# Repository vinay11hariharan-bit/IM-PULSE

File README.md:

# IM-PULSE — Cuffless Blood Pressure & Cardiac Monitor

**🏆 Top-10 finalist, EDL 2026, IIT Bombay**

IM-PULSE is a compact, portable biomedical monitor built in the Electronic Device Lab (EDL) course at IIT Bombay. It acquires ECG and two arterial pulse waveforms (APW, from bioimpedance/IPG) through six electrodes on the chest and foot. It detects ECG R-peaks and APW feet on board, measures **pulse transit time (PTT)** and **pulse wave velocity** (4–10 m/s), and estimates **blood pressure without a cuff** using an XGBoost model. Data streams wirelessly to a laptop, which shows a live PyQt6 dashboard and serves the vitals to any browser through a Flask web server.

The aim is a convenient alternative to bulky inflatable-cuff BP monitors and conventional ECG / Bio-Z instruments, for frequent cardiac monitoring where such equipment is unavailable or unaffordable.

## System Overview

```
 6 electrodes (chest, foot, abdomen ref.)
        │
 2 × MAX30001 AFE  ── ECG + BioZ @ 128 Hz ──┐
                                            ▼  SPI
 INA219 power monitor ── I2C ──►  STM32F411 Black Pill
                                   • Pan-Tompkins R-peak detection (ECG)
                                   • APW foot detection (proximal: ECG-triggered cubic fit,
                                     distal: morphological V-shape detector)
                                   • 36-byte packet every 8 ms
                                            │  UART 57600
                                            ▼
                                   ESP32  ── UDP broadcast, port 12345 (Wi-Fi)
                                            │
                                            ▼
                     Laptop: display.py (PyQt6)                webserver.py (Flask + ngrok)
                     • PTT, PWV, heart rate, HRV       ──►     • browser dashboard on LAN
                     • ECG morphology (QRS, PR, QTc)   JSON    or the internet
                     • XGBoost BP estimate
```

| | |
|---|---|
| Acquisition | 2 × MAX30001 (ECG + bioimpedance), 128 Hz per channel |
| Processing MCU | STM32F411CEU6 (Cortex-M4F, 100 MHz) |
| Wireless | ESP32, UART → UDP over Wi-Fi |
| Power | 2 × 18650 Li-ion with BMS, INA219 telemetry |
| Hardware | Custom two-layer PCB (KiCad), 3D-printed enclosure with acrylic panels |
| Host software | Python: PyQt6 + pyqtgraph GUI, Flask dashboard, XGBoost BP model |

## Repository Layout

| Path | Contents |
|---|---|
| [`src/stm32_blackpill/`](src/stm32_blackpill) | Acquisition and on-board DSP firmware (Arduino / STM32duino) |
| [`src/esp32_bridge/`](src/esp32_bridge) | UART-to-UDP Wi-Fi bridge firmware |
| [`src/host_app/`](src/host_app) | Desktop GUI (`display.py`), web dashboard (`webserver.py`), trained BP model |
| [`pcb/`](pcb) | KiCad project for the device PCB, footprints, layer prints, BMS build photos |
| [`3d_models/`](3d_models) | Enclosure STL and laser-cut acrylic panel DXFs |
| [`others/`](others) | [User manual](others/USER_MANUAL.md), build photos, MATLAB simulations, BMS docs, write-ups |
| [`reports/`](reports) | Milestone reports M0–M4 |
| [`bom.xls`](bom.xls) | Bill of materials |

Every folder has its own README with details. Each firmware/software folder also has a `SETUP.md` with flashing or run instructions.

## Quick Start

1. **STM32** — flash `src/stm32_blackpill/stm32_blackpill.ino` with the STM32duino core ([setup](src/stm32_blackpill/SETUP.md)).
2. **ESP32** — put your Wi-Fi SSID and password in `src/esp32_bridge/esp32_bridge.ino`, then flash it ([setup](src/esp32_bridge/SETUP.md)).
3. **Laptop** — join the same network, then run:
   ```sh
   cd src/host_app
   pip install -r requirements.txt
   python display.py      # live GUI + signal processing
   python webserver.py    # in a second terminal: browser dashboard on port 5000
   ```
   See [`src/host_app/SETUP.md`](src/host_app/SETUP.md) for virtual-environment and ngrok setup, and the [user manual](others/USER_MANUAL.md) for electrode placement.

## Build Photos

| PCB | Assembled device | Enclosure |
|---|---|---|
|  |  |  |

## Team

IM-PULSE (group MON-04): Yashvardhan Khandegar, Sudhindra Sahoo, Jahnvi Sharma, Vinay Hariharan, Krunal Vaghela.

---

# Reflections, Challenges & Future Work

### Project Status Summary

| Specification / Requirement | Status | Remarks / Justification |
|:----------------------------|:------:|:------------------------|
| 4-electrodes only, two on each wrist | ⚠️ Incomplete | Wrist APW unviable — instead we used 6 electrodes (chest (2) + foot (2) + abdomen reference (2)) |
| Compact portable table-top unit (bio-signal acquisition, processing & wireless) | ✅ Complete | |
| Onboard ECG R-peak & APW foot detection on STM32 | ✅ Complete | |
| Plot ECG + proximal & distal APW, verify reliability | 🔶 Partial | Chest ECG & APW reliable; foot APW less regular due to lower SNR — heart rate cross-verified with clinical device |
| Obtain Pulse Wave Velocity in typical range (4–10 m/s) | ✅ Complete | |
| Derive other health parameters from PTT and cross-verify them | 🔶 Partial | We focused on blood pressure as research has shown negative PTT–BP correlation; model trained on single subject (data limitation) |

---

### Challenges & How We Overcame Them

#### Dual-Purpose BioZ (Respiration + APW for PTT)

**Problem:** The MAX30001's BioZ channel conflates respiration and blood-related IPG signals. Respiration-focused acquisition introduced a DC offset and saturation, distorting the APW signal needed for PTT computation.

**Solution:** We reconfigured the channel for blood IPG (APW) by removing respiration-centric filtering, applying a band-pass filter (~0.8–5 Hz), and syncing the APW with ECG R-peaks to correctly compute PTT.

---

#### Electrode Placement & Signal Integrity

**Problem:** Accurate proximal–distal APW measurement required very precise electrode placement, and signals were frequently distorted by environmental interference from nearby charged sources.

**Solution:** After extensive experimentation, we finalized electrode positions over the chest (proximal) and left foot (distal) arteries to capture stable APW. Interference was eliminated by grounding nearby charged objects in the measurement environment.

---

#### PTT–BP Modeling with a Custom Dataset

**Problem:** No reliable publicly available dataset exists for heart-to-foot PTT vs blood pressure correlation. Our raw measurements were noisy and unstructured, making it difficult to train a meaningful model.

**Solution:** We collected approximately 200 samples using reference blood pressure measurements alongside our PTT readings, cleaned and processed the raw data, and trained a regression model to learn the PTT–BP mapping and extract meaningful patterns.

---

#### STM32 Chip Mismatch (F411CE vs F401CE)

**Problem:** The BlackPill boards purchased were labelled STM32F411CE, but many units in the market are actually equipped with an STM32F401CE chip. This silent mismatch caused repeated code upload failures and cost significant debugging time before the root cause was identified.

**What We Learned:** Always verify the actual chip ID using STM32CubeProgrammer before beginning development. Physical markings on a board cannot always be trusted, especially with generic suppliers.

---

### Key Takeaways

**Technical:**
- Bio-signal acquisition requires careful analog front-end tuning — default configurations are rarely sufficient for multi-purpose sensors like the MAX30001.
- Electrode placement has a profound impact on signal quality; this is as much a physiological problem as an electronics one.
- Building a custom dataset from scratch is time-consuming but necessary when the target measurement (heart-to-foot PTT) does not have existing benchmarks.
- Hardware debugging (chip mismatches, board variants) can consume a disproportionate amount of time — always validate components early.

**Team & Process:**
- A modular PCB and software architecture paid off: when individual components failed or needed replacement, the rest of the system remained unaffected.
- Separating the signal processing pipeline from the hardware layer early allowed the software team to develop and test algorithms in parallel with PCB bring-up.
- Time lost on hardware issues compressed the software iteration cycles — future projects should budget extra time for hardware validation in the first two weeks.

---

## Incomplete Features & Future Work

### Features Not Completed Within the Course Timeline

- **Wrist-based APW measurement:** The original specification required only 4 electrodes placed on the wrists. Wrist APW turned out to be physiologically unviable for our sensing configuration — the signal was too weak and inconsistent for reliable PTT computation. This remains unresolved.
- **Multi-subject PTT–BP model:** The trained blood pressure model was built on data from a single subject due to time constraints. A generalised model requires a larger and more diverse dataset, which was not feasible within the semester.
- **Full cross-verification of derived health parameters:** While blood pressure estimation via PTT was partially achieved, other health parameters derivable from PTT (e.g., arterial stiffness index) were not implemented or verified.

---

### Concrete Future Work

**1. Expand the PTT–BP dataset and improve the model**
The current model is trained on a single subject (~200 samples), which limits its generalisability. Future work would involve collecting data across multiple subjects with varying age, fitness levels, and blood pressure ranges, and retraining the model. A more robust architecture (e.g., a subject-adaptive or personalised calibration model) could significantly improve accuracy.

**2. Improve foot APW signal quality with better analog filtering**
The foot APW signal had lower SNR compared to the chest signal. This could be addressed by adding a programmable gain stage or a narrower band-pass filter specifically tuned for the distal IPG signal, implemented either in hardware (op-amp filter stage on PCB) or through tighter DSP filtering on the STM32.

**3. Investigate wrist-based electrode configuration**
The wrist APW failure could be revisited by exploring different electrode configurations (e.g., radial artery targeting) or switching to PPG-based sensing at the wrist as a complementary approach for PTT. This would bring the device closer to the original wearable specification.

**4. Reduce wireless latency for real-time monitoring**
The current UDP-over-WiFi transmission introduces latency that makes real-time waveform monitoring less smooth. Switching to a lower-latency protocol (e.g., BLE with a custom GATT profile) or implementing a lightweight compression scheme before transmission could improve the live display experience without requiring a wired connection.

**5. Onboard blood pressure display**
Currently, BP estimation requires post-processing on a connected laptop. Integrating a small OLED display on the device and running the trained model directly on the ESP32 (after model quantisation) would make the device fully self-contained and usable without a computer.

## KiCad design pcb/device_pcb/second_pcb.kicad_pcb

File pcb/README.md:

# PCB Design 

## Overview

The primary purpose of this PCB is to provide an organized and compact physical realization of the circuit. It is basically a Bio-Signal Acquisition Board. Most components are breakout/evaluation boards that are directly fixed onto the PCB using female header pins, with the PCB establishing the required electrical connections between them.

<!-- Board photo -->

<!-- Board photo -->

---

## Features & Design Choices

### Two-Layer PCB with Ground Planes
SMD components are placed on the top layer, with a ground plane on both the top and bottom layers. Using ground planes on both sides helps shield signals from noise and provides a stable return path. Placing all components on the top layer simplifies the assembly process for both SMD and Through-Hole components. The continuous ground plane on the bottom layer also aids in heat dissipation due to the larger copper area.

### Modular PCB Design
Since the main goal of this project is building the software stack for bio-signal processing, the PCB is designed to act as an integration unit for power and signal connections between different modules. This modular setup keeps the focus on algorithms and makes it easy to replace individual parts if they are damaged.

### Indicator LEDs & Breakout Pins for Debugging
Built-in test points in the form of indicator LEDs and breakout pins make it easier to monitor power and signal lines, and to troubleshoot issues using an oscilloscope or multimeter. 
- One red-colored POWER LED
- Two yellow-colored LEDs to indicate which of the MAX30001 has been selected
- There are a few pins broken-out from the STM32 and the ESP32 such as general GPIO, SPI/UART lines for expanding functionality as well as debugging.  

### Power Stability
The PCB requires a stable & regulated 5V input at its main screw terminal. The STM32 has onboard 5V to 3V3 regulator, which then distributes a stable 3V3 voltage to other components. Decoupling capacitors are placed at the power inputs and outputs of each module to filter out electrical noise and maintain stable voltage levels.

---

## Components & Signal Flow

### Bio-Signal Acquisition — MAX30001 (×2)
Two **Protocentral MAX30001** breakout boards are used for collecting:
- **ECG** (Electrocardiogram) signals
- **Bio-Z** (Bioimpedance) signals

Both boards interface with the STM32 via **SPI**.

### Main MCU — STM32 BlackPill
The STM32 serves as the central processing unit of the system. It:
- Receives raw bio-signal data from both MAX30001 boards over SPI
- Runs on-board DSP algorithms for **ECG R-peak detection** and **APW (Arterial Pulse Wave) foot detection**
- Communicates with the INA219 over **I2C**
- Transmits processed data to the ESP32 over **UART (TX/RX)**

### Power Monitoring — INA219
The **INA219** current/power sensor is connected to the STM32 via **I2C**. It provides real-time data on:
- Battery voltage
- Current draw

### Wireless Communication — ESP32
The **ESP32** is connected to the STM32 via **UART**. It:
- Receives data packets containing waveform data, detected special points (R-peaks, APW feet), and INA219 readings
- Generates a **Wi-Fi access point** for wireless connectivity
- Transmits data to connected clients (e.g., laptops) using the **UDP** protocol

---

## System Architecture

```
┌─────────────────┐     SPI      ┌────────────────────┐
│  MAX30001 #1    │─────────────▶│                    │
│  (ECG / Bio-Z)  │              │   STM32 BlackPill  │──── I2C ────▶ INA219
└─────────────────┘              │   (DSP + Control)  │
                                 │                    │──── UART ───▶ ESP32 ──▶ WiFi (UDP)
┌─────────────────┐     SPI      │                    │
│  MAX30001 #2    │─────────────▶│                    │
│  (ECG / Bio-Z)  │              └────────────────────┘
└─────────────────┘
```

---

## Communication Interfaces Summary

| Interface | Between | Purpose |
|-----------|---------|---------|
| SPI | STM32 ↔ MAX30001 (×2) | Bio-signal data acquisition |
| I2C | STM32 ↔ INA219 | Battery voltage & current monitoring |
| UART | STM32 ↔ ESP32 | Processed data transfer |
| UDP (Wi-Fi) | ESP32 ↔ Client Device | Wireless data streaming |

## Pin Connections
 
### MAX30001 Board 1 → STM32 (SPI)
 
| MAX30001 Pin | STM32 Pin | Notes |
|:-------------|:----------|:------|
| GND | GND | |
| VCC | 3V3 | |
| GND | GND | |
| INT2 | — | Not Connected |
| INT1 | PB10 | Interrupt line |
| FCLK | — | Not Connected (external CLK not used) |
| CS0 | PB0 | Chip Select |
| SCK | PA5 | SPI1 Clock |
| MOSI | PA7 | SPI1 MOSI |
| MISO | PA6 | SPI1 MISO |
 
### MAX30001 Board 2 → STM32 (SPI)
 
| MAX30001 Pin | STM32 Pin | Notes |
|:-------------|:----------|:------|
| GND | GND | |
| VCC | 3V3 | |
| GND | GND | |
| INT2 | — | Not Connected |
| INT1 | PA1 | Interrupt line |
| FCLK | — | Not Connected (external CLK not used) |
| CS0 | PA0 | Chip Select |
| SCK | PA5 | SPI1 Clock (shared) |
| MOSI | PA7 | SPI1 MOSI (shared) |
| MISO | PA6 | SPI1 MISO (shared) |
 
> **Note:** Both MAX30001 boards share the same SPI bus (SCK, MOSI, MISO). They are differentiated by their individual Chip Select (CS0) pins — PB0 and PA0 respectively.
 
### INA219 → STM32 (I2C)
 
| INA219 Pin | STM32 / Connection | Notes |
|:-----------|:-------------------|:------|
| VCC | 3V3 | |
| GND | GND | |
| SCL | PB6 | I2C1 Clock |
| SDA | PB7 | I2C1 Data |
| Vin+ | Battery (+) terminal | High-side current sensing |
| Vin− | Switch output | Connected via the power switch |
 
### ESP32 → STM32 (UART)
 
| ESP32 Pin | STM32 Pin | Notes |
|:----------|:----------|:------|
| TX2 | PA10 (RX1) | ESP32 transmits → STM32 receives |
| RX2 | PA9 (TX1) | STM32 transmits → ESP32 receives |
 
---
 
## Known Issues & Gotchas
 
### ⚠️ STM32F411CE vs STM32F401CE Chip Mismatch
 
The STM32 BlackPill boards purchased were labelled as **STM32F411CE**, however many units sold in the market are actually equipped with an **STM32F401CE** chip. This mismatch is not visible externally and caused significant time loss during development when code uploads were failing unexpectedly.
 
**Root cause:** Counterfeit or mislabelled boards — the chip inscription on the package does not always match the actual silicon inside.
 
**How to detect:** Open **STM32CubeProgrammer**, connect via ST-Link, and check the **Device ID** reported by the programmer. This will reveal the actual chip variant regardless of what is printed on the board.
 
**Fix:** Once the correct chip is identified (e.g., `STM32F401CE`), select the matching target in STM32CubeIDE / STM32CubeMX and re-generate the project configuration.
 
---
 
## Component Links
 
| Component | Supplier | Link |
|:----------|:---------|:-----|
| Protocentral MAX30001 ECG & Bio-Z Breakout (×2) | Protocentral | [protocentral.com](https://protocentral.com/product/protocentral-max30001/) |
| STM32F411CEU6 BlackPill (WeAct Studio) | Robu.in | [robu.in](https://robu.in/product/weact-studio-blackpill-stm32f411ceu6-f411-25m-hse-core-learning-board-micropython-development/) |
| STM32F411CEU6 Minimum System Board | Robu.in | [robu.in](https://robu.in/product/stm32f411ceu6-minimum-system-board-microcomputer-stm32-arm-core-board/) |
| INA219 Current/Power Monitor (CJMCU-219) | Robu.in | [robu.in](https://robu.in/product/cjmcu-219-ina219-i2c-interface-no-drift-bi-directional-current-power-monitoring-sensor-module/) |
| ESP32 WROOM-32 Development Board | Robu.in | [robu.in](https://robu.in/product/esp32-38pin-development-board-wifibluetooth-ultra-low-power-consumption-dual-core/) |
| ST-Link V2 Programmer (for flashing STM32) | Robu.in | [robu.in](https://robu.in/product/st-link-v2-programmer-for-stm8-and-stm32/) |
 
> **Note:** The MAX30001 is a Protocentral product and is not available on Robu.in. Purchase directly from [protocentral.com](https://protocentral.com/product/protocentral-max30001/).

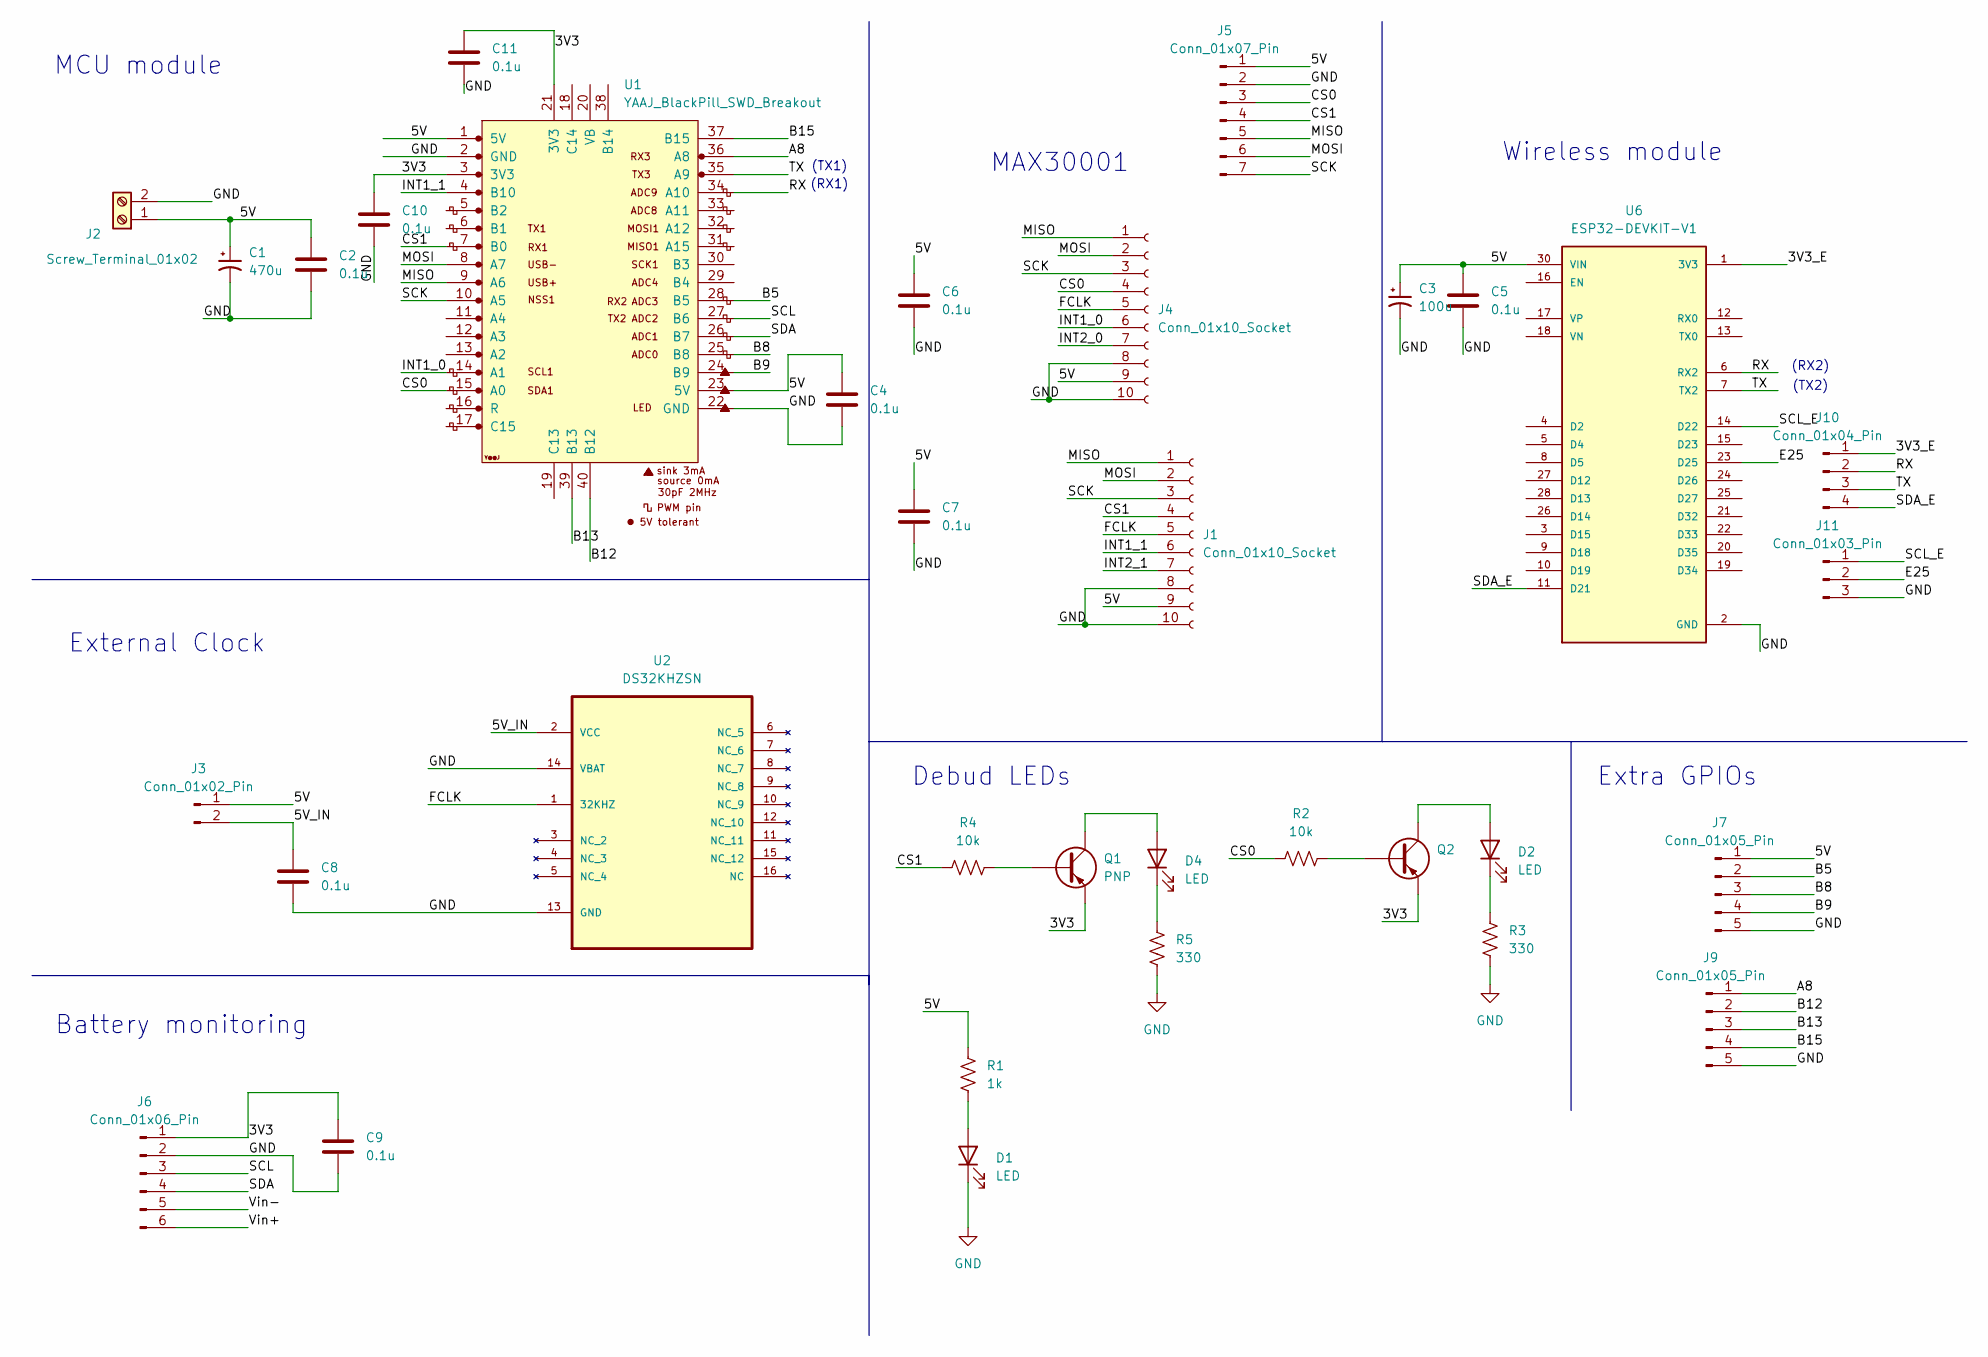
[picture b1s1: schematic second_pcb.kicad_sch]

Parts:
C1: 470u; CP_Radial_D8.0mm_P3.50mm
C2, C4, C5, C6, C7, C8, C9, C10, C11: 0.1u; C_0805_2012Metric
C3: 100u; CP_Radial_D5.0mm_P2.50mm
D1, D2, D4: LED; LED_1206_3216Metric
J1, J4: Conn_01x10_Socket; PinHeader_1x10_P2.54mm_Vertical
J2: Screw_Terminal_01x02; TerminalBlock_Phoenix_MKDS-3-2-5.08_1x02_P5.08mm_Horizontal
J3: Conn_01x02_Pin; PinHeader_1x02_P2.54mm_Vertical
J5: Conn_01x07_Pin; PinHeader_1x07_P2.54mm_Vertical
J6: Conn_01x06_Pin; PinHeader_1x06_P2.54mm_Vertical
J7, J9: Conn_01x05_Pin; PinHeader_1x05_P2.54mm_Vertical
J10: Conn_01x04_Pin; PinHeader_1x04_P2.54mm_Vertical
J11: Conn_01x03_Pin; PinHeader_1x03_P2.54mm_Vertical
Q1, Q2: PNP; TO-92L_HandSolder_modified
R1: 1k; R_0805_2012Metric
R2, R4: 10k; R_0805_2012Metric
R3, R5: 330; R_0805_2012Metric
U1: YAAJ_BlackPill_SWD_Breakout; YAAJ_BluePill_SWD_1
U2: DS32KHZSN; SOIC127P1034X267-16N; MPN DS32KHZSN#
U6: ESP32-DEVKIT-V1; MODULE_ESP32_DEVKIT_V1_modified; PARTREV N/A

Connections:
/3V3: C9.2, C10.2, C11.2, J6.1, Q1.1 (E), Q2.1 (E), U1.3 (3V3), U1.21 (3V3)
/3V3_E: J10.1, U6.1 (3V3)
/5V: C1.1, C2.2, C3.1, C4.2, C5.2, C6.2, C7.2, J1.9, J2.1, J3.1, J4.9, J5.1, J7.1, R1.1, U1.1 (5V), U1.23 (5V), U6.30 (VIN)
/5V_IN: C8.2, J3.2, U2.2 (VCC)
/A8: J9.1, U1.36 (A8)
/B5: J7.2, U1.28 (B5)
/B8: J7.3, U1.25 (B8)
/B9: J7.4, U1.24 (B9)
/B12: J9.2, U1.40 (B12)
/B13: J9.3, U1.39 (B13)
/B15: J9.4, U1.37 (B15)
/CS0: J4.4, J5.3, R2.1, U1.15 (A0)
/CS1: J1.4, J5.4, R4.1, U1.7 (B0)
/E25: J11.2, U6.23 (D25)
/FCLK: J1.5, J4.5, U2.1 (32KHZ)
/INT1_0: J4.6, U1.14 (A1)
/INT1_1: J1.6, U1.4 (B10)
/INT2_0: J4.7
/INT2_1: J1.7
/MISO: J1.1, J4.1, J5.5, U1.9 (A6)
/MOSI: J1.2, J4.2, J5.6, U1.8 (A7)
/RX: J10.2, U1.34 (A10), U6.6 (RX2)
/SCK: J1.3, J4.3, J5.7, U1.10 (A5)
/SCL: J6.3, U1.27 (B6)
/SCL_E: J11.1, U6.14 (D22)
/SDA: J6.4, U1.26 (B7)
/SDA_E: J10.4, U6.11 (D21)
/TX: J10.3, U1.35 (A9), U6.7 (TX2)
/Vin+: J6.6
/Vin-: J6.5
GND: C1.2, C2.1, C3.2, C4.1, C5.1, C6.1, C7.1, C8.1, C9.1, C10.1, C11.1, D1.1 (K), J1.8, J1.10, J2.2, J4.8, J4.10, J5.2, J6.2, J7.5, J9.5, J11.3, R3.1, R5.1, U1.2 (GND), U1.22 (GND), U2.13 (GND), U2.14 (VBAT), U6.2 (GND), U6.29 (GND)
unnamed: D1.2 (A), R1.2
unnamed: D2.2 (A), Q2.3 (C)
unnamed: D2.1 (K), R3.2
unnamed: D4.2 (A), Q1.3 (C)
unnamed: D4.1 (K), R5.2
unnamed: Q1.2 (B), R4.2
unnamed: Q2.2 (B), R2.2

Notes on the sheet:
Debud LEDs
External Clock
Wireless module
Battery monitoring
MCU module
(RX2)
Extra GPIOs
MAX30001
(TX2)
(TX1)
(RX1)

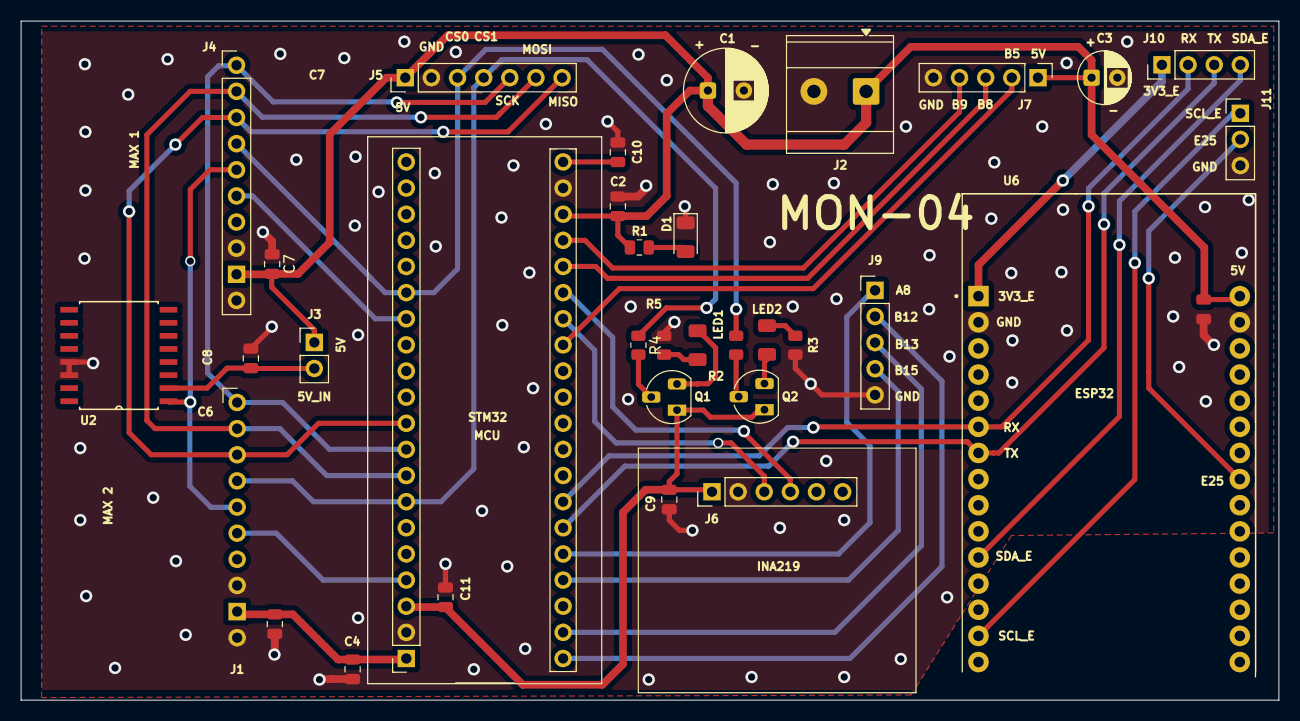
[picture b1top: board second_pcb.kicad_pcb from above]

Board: 2 copper layers, 122.2 x 66.0 mm, 34 parts (0 on the bottom side), 34 nets.
